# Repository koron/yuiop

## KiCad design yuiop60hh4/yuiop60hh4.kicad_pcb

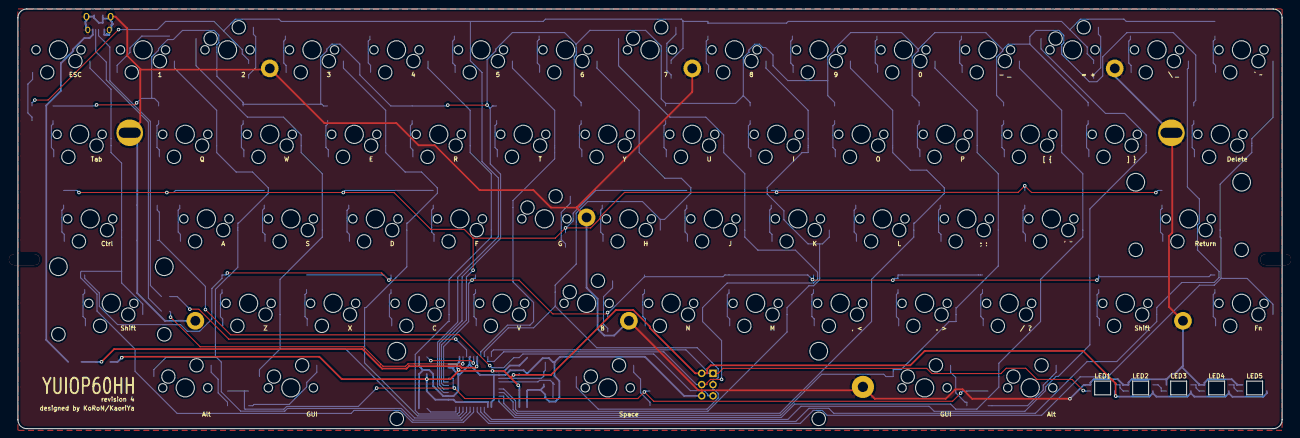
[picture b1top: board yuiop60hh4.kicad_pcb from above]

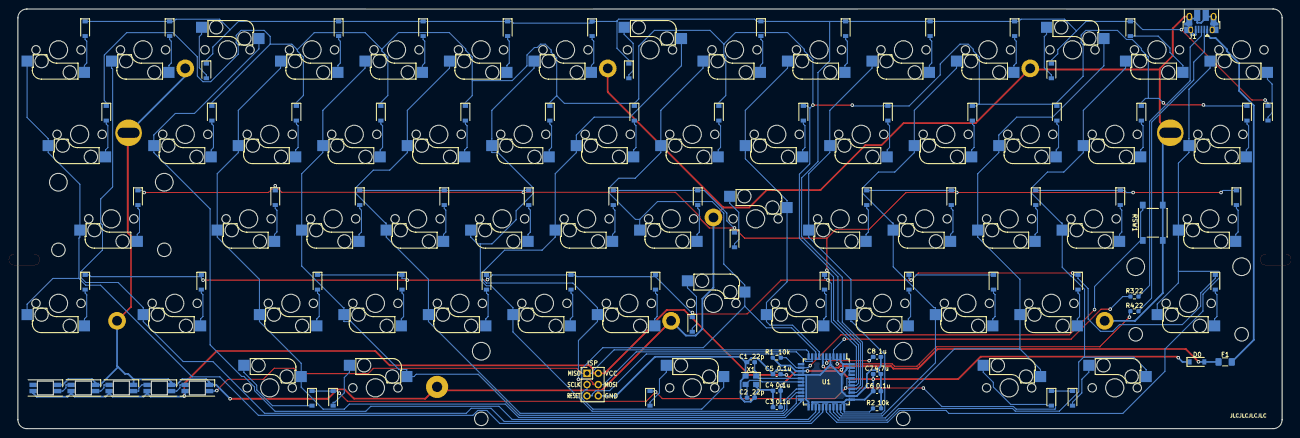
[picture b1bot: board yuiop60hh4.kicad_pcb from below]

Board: 2 copper layers, 285.0 x 94.6 mm, 159 parts (19 on the bottom side), 98 nets.

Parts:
C1, C2: 22p; C_0603_1608Metric_Pad1.08x0.95mm_HandSolder
C3, C4, C5, C6: 0.1u; C_0603_1608Metric_Pad1.08x0.95mm_HandSolder
C7: 4.7u; C_0603_1608Metric_Pad1.08x0.95mm_HandSolder
C8: 1u; C_0603_1608Metric_Pad1.08x0.95mm_HandSolder
D0: D_Schottky; D_SOD-123
D1, D2, D3, D4, D5, D6, D7, D8, D9, D10, D11, D12, D13, D14, D15, D16, D17, D18, D19, D20, D21, D22, D23, D24, D25, D26, D27, D28, D29, D30, D31, D32, D33, D34, D35, D36, D37, D38, D39, D40, D41, D42, D43, D44, D45, D46, D47, D48, D49, D50, D51, D52, D53, D54, D55, D56, D57, D58, D59, D60: 1N4148W; D_SOD-123
F1: Fuse; Fuse_1206_3216Metric_Pad1.42x1.75mm_HandSolder
HOLE1, HOLE2, HOLE4: Hole_5x2.3_6; Hole_5x2.5_7
HOLE3: Hole_2.3; Hole_5x2.5_7
HOLE5, HOLE6: Hole_7x2.5; Hole_7x2.5_10x5
HOLE7, HOLE8, HOLE9, HOLE10, HOLE11, HOLE12: Hole_2.2_4
J1: USB_B_Micro; USB_Micro-B_Amphenol_10103594-0001LF_Horizontal
J2: ISP; PinHeader_2x03_P2.54mm_Vertical
KSW1: ESC; Cherry_MX_Hotswap_1.0u
KSW2: 1; Cherry_MX_Hotswap_1.0u
KSW3: 2; Cherry_MX_Hotswap_1.0u
KSW4: 3; Cherry_MX_Hotswap_1.0u
KSW5: 4; Cherry_MX_Hotswap_1.0u
KSW6: 5; Cherry_MX_Hotswap_1.0u
KSW7: 6; Cherry_MX_Hotswap_1.0u
KSW8: 7; Cherry_MX_Hotswap_1.0u
KSW9: 8; Cherry_MX_Hotswap_1.0u
KSW10: 9; Cherry_MX_Hotswap_1.0u
KSW11: 0; Cherry_MX_Hotswap_1.0u
KSW12: - _; Cherry_MX_Hotswap_1.0u
KSW13: = +; Cherry_MX_Hotswap_1.0u
KSW14: \ _; Cherry_MX_Hotswap_1.0u
KSW15: ` ~~; Cherry_MX_Hotswap_1.0u
KSW16: Tab; Cherry_MX_Hotswap_1.0u
KSW17: Q; Cherry_MX_Hotswap_1.0u
KSW18: W; Cherry_MX_Hotswap_1.0u
KSW19: E; Cherry_MX_Hotswap_1.0u
KSW20: R; Cherry_MX_Hotswap_1.0u
KSW21: T; Cherry_MX_Hotswap_1.0u
KSW22: Y; Cherry_MX_Hotswap_1.0u
KSW23: U; Cherry_MX_Hotswap_1.0u
KSW24: I; Cherry_MX_Hotswap_1.0u
KSW25: O; Cherry_MX_Hotswap_1.0u
KSW26: P; Cherry_MX_Hotswap_1.0u
KSW27: [ {; Cherry_MX_Hotswap_1.0u
KSW28: ] }; Cherry_MX_Hotswap_1.0u
KSW29: Delete; Cherry_MX_Hotswap_1.0u
KSW30: Ctrl; Cherry_MX_Hotswap_1.0u
KSW31: A; Cherry_MX_Hotswap_1.0u
KSW32: S; Cherry_MX_Hotswap_1.0u
KSW33: D; Cherry_MX_Hotswap_1.0u
KSW34: F; Cherry_MX_Hotswap_1.0u
KSW35: G; Cherry_MX_Hotswap_1.0u
KSW36: H; Cherry_MX_Hotswap_1.0u
KSW37: J; Cherry_MX_Hotswap_1.0u
KSW38: K; Cherry_MX_Hotswap_1.0u
KSW39: L; Cherry_MX_Hotswap_1.0u
KSW40: ; :; Cherry_MX_Hotswap_1.0u
KSW41: ' "; Cherry_MX_Hotswap_1.0u
KSW42: Return; Cherry_MX_Hotswap_1.0u
KSW43, KSW54: Shift; Cherry_MX_Hotswap_1.0u
KSW44: Z; Cherry_MX_Hotswap_1.0u
KSW45: X; Cherry_MX_Hotswap_1.0u
KSW46: C; Cherry_MX_Hotswap_1.0u
KSW47: V; Cherry_MX_Hotswap_1.0u
KSW48: B; Cherry_MX_Hotswap_1.0u
KSW49: N; Cherry_MX_Hotswap_1.0u
KSW50: M; Cherry_MX_Hotswap_1.0u
KSW51: , <; Cherry_MX_Hotswap_1.0u
KSW52: . >; Cherry_MX_Hotswap_1.0u
KSW53: / ?; Cherry_MX_Hotswap_1.0u
KSW55: Fn; Cherry_MX_Hotswap_1.0u
KSW56, KSW60: Alt; Cherry_MX_Hotswap_1.0u
KSW57, KSW59: GUI; Cherry_MX_Hotswap_1.0u
KSW58: Space; Cherry_MX_Hotswap_1.0u
LED1, LED2, LED3, LED4, LED5: SK6812MINI; SK6812MINI-E_B
R1, R2: 10k; R_0603_1608Metric_Pad0.98x0.95mm_HandSolder
R3, R4: 22; R_0603_1608Metric_Pad0.98x0.95mm_HandSolder
RSW1: RESET; SW_Push_1P1T_NO_6x6mm_H9.5mm
STB1, STB3: Cherry_MX_Stabilizer
STB2: Cherry_MX_Stabilizer_6.0u
U1: ATmega32U4-AU; TQFP-44_10x10mm_P0.8mm
X1: XTAL; Oscillator_SMD_SeikoEpson_SG8002CE-4Pin_3.2x2.5mm

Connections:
/COL_01: KSW1.1, KSW16.1, KSW30.1, KSW43.1, U1.28
/COL_02: KSW2.1, KSW17.1, KSW31.1, KSW56.1, U1.29
/COL_03: KSW3.1, KSW18.1, KSW32.1, KSW44.1, KSW57.1, U1.30
/COL_04: KSW4.1, KSW19.1, KSW33.1, KSW45.1, U1.31
/COL_05: KSW5.1, KSW20.1, KSW34.1, KSW46.1, U1.32
/COL_06: KSW6.1, KSW21.1, KSW35.1, KSW47.1, U1.8
/COL_07: J2.3, KSW7.1, KSW22.1, KSW36.1, KSW48.1, KSW58.1, U1.9
/COL_08: J2.4, KSW8.1, KSW23.1, KSW37.1, KSW49.1, U1.10
/COL_09: KSW9.1, KSW24.1, KSW38.1, KSW50.1, U1.19
/COL_10: KSW10.1, KSW25.1, KSW39.1, KSW51.1, U1.20
/COL_11: KSW11.1, KSW26.1, KSW40.1, KSW52.1, KSW59.1, U1.21
/COL_12: KSW12.1, KSW27.1, KSW41.1, KSW53.1, KSW60.1, U1.22
/COL_13: KSW13.1, KSW28.1, U1.25
/COL_14: KSW14.1, KSW54.1, U1.26
/COL_15: KSW15.1, KSW29.1, KSW42.1, KSW55.1, U1.27
/Controller/D+: R3.1, U1.4
/Controller/D-: R4.1, U1.3
/Controller/V_USB: D0.2, F1.1, U1.7
/Controller/XTAL1: C2.1, U1.17, X1.3
/Controller/XTAL2: C1.1, U1.16, X1.1
/LED_DATA: J2.1, LED1.4, U1.11
/RESET: J2.5, R1.2, RSW1.1, U1.13
/ROW_1: D1.1, D2.1, D3.1, D4.1, D5.1, D6.1, D7.1, D8.1, D9.1, D10.1, D11.1, D12.1, D13.1, D14.1, D15.1, U1.36
/ROW_2: D16.1, D17.1, D18.1, D19.1, D20.1, D21.1, D22.1, D23.1, D24.1, D25.1, D26.1, D27.1, D28.1, D29.1, U1.37
/ROW_3: D30.1, D31.1, D32.1, D33.1, D34.1, D35.1, D36.1, D37.1, D38.1, D39.1, D40.1, D41.1, D42.1, U1.38
/ROW_4: D43.1, D44.1, D45.1, D46.1, D47.1, D48.1, D49.1, D50.1, D51.1, D52.1, D53.1, D54.1, D55.1, U1.39
/ROW_5: D56.1, D57.1, D58.1, D59.1, D60.1, U1.40
/USB_D+: J1.3, R3.2
/USB_D-: J1.2, R4.2
/USB_VBUS: F1.2, J1.1
GND: C1.2, C2.2, C3.2, C4.2, C5.2, C6.2, C7.2, C8.1, J1.5, J1.6, J2.6, LED1.3, LED2.3, LED3.3, LED4.3, LED5.3, R2.1, RSW1.2, U1.5, U1.15, U1.23, U1.35, U1.43, X1.2, X1.4
unnamed: C8.2, U1.6
unnamed: D1.2, KSW1.2
unnamed: D2.2, KSW2.2
unnamed: D3.2, KSW3.2
unnamed: D4.2, KSW4.2
unnamed: D5.2, KSW5.2
unnamed: D6.2, KSW6.2
unnamed: D7.2, KSW7.2
unnamed: D8.2, KSW8.2
unnamed: D9.2, KSW9.2
unnamed: D10.2, KSW10.2
unnamed: D11.2, KSW11.2
unnamed: D12.2, KSW12.2
unnamed: D13.2, KSW13.2
unnamed: D14.2, KSW14.2
unnamed: D15.2, KSW15.2
unnamed: D16.2, KSW16.2
unnamed: D17.2, KSW17.2
unnamed: D18.2, KSW18.2
unnamed: D19.2, KSW19.2
unnamed: D20.2, KSW20.2
unnamed: D21.2, KSW21.2
unnamed: D22.2, KSW22.2
unnamed: D23.2, KSW23.2
unnamed: D24.2, KSW24.2
unnamed: D25.2, KSW25.2
unnamed: D26.2, KSW26.2
unnamed: D27.2, KSW27.2
unnamed: D28.2, KSW28.2
unnamed: D29.2, KSW29.2
unnamed: D30.2, KSW30.2
unnamed: D31.2, KSW31.2
unnamed: D32.2, KSW32.2
unnamed: D33.2, KSW33.2
unnamed: D34.2, KSW34.2
unnamed: D35.2, KSW35.2
unnamed: D36.2, KSW36.2
unnamed: D37.2, KSW37.2
unnamed: D38.2, KSW38.2
unnamed: D39.2, KSW39.2
unnamed: D40.2, KSW40.2
unnamed: D41.2, KSW41.2
unnamed: D42.2, KSW42.2
unnamed: D43.2, KSW43.2
unnamed: D44.2, KSW44.2
unnamed: D45.2, KSW45.2
unnamed: D46.2, KSW46.2
unnamed: D47.2, KSW47.2
unnamed: D48.2, KSW48.2
unnamed: D49.2, KSW49.2
unnamed: D50.2, KSW50.2
unnamed: D51.2, KSW51.2
unnamed: D52.2, KSW52.2
unnamed: D53.2, KSW53.2
unnamed: D54.2, KSW54.2
unnamed: D55.2, KSW55.2
unnamed: D56.2, KSW56.2
unnamed: D57.2, KSW57.2
unnamed: D58.2, KSW58.2
unnamed: D59.2, KSW59.2
unnamed: D60.2, KSW60.2
unnamed: LED1.2, LED2.4
unnamed: LED2.2, LED3.4
unnamed: LED3.2, LED4.4
unnamed: LED4.2, LED5.4
unnamed: R2.2, U1.33
VCC: C3.1, C4.1, C5.1, C6.1, C7.1, D0.1, J2.2, LED1.1, LED2.1, LED3.1, LED4.1, LED5.1, R1.1, U1.2, U1.14, U1.24, U1.34, U1.44

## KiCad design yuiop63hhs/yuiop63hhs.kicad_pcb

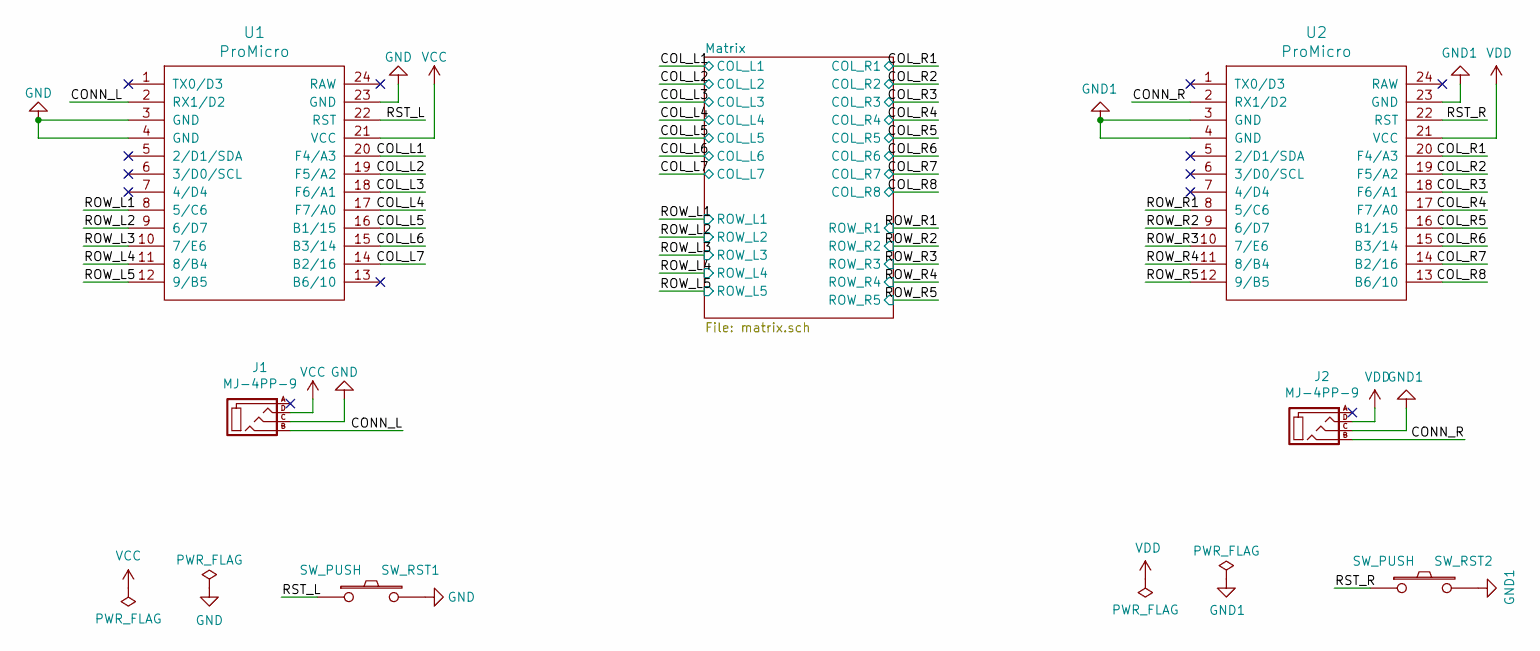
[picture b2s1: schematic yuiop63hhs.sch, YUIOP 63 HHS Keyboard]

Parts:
J1, J2: MJ-4PP-9; MJ-4PP-9_1side
SW_RST1, SW_RST2: SW_PUSH; ResetSW_2_1side
U1, U2: ProMicro; ProMicro_v3

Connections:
/COL_L1: U1.20 (F4/A3); also elsewhere on the board
/COL_L2: U1.19 (F5/A2); also elsewhere on the board
/COL_L3: U1.18 (F6/A1); also elsewhere on the board
/COL_L4: U1.17 (F7/A0); also elsewhere on the board
/COL_L5: U1.16 (B1/15); also elsewhere on the board
/COL_L6: U1.15 (B3/14); also elsewhere on the board
/COL_L7: U1.14 (B2/16); also elsewhere on the board
/COL_R1: U2.20 (F4/A3); also elsewhere on the board
/COL_R2: U2.19 (F5/A2); also elsewhere on the board
/COL_R3: U2.18 (F6/A1); also elsewhere on the board
/COL_R4: U2.17 (F7/A0); also elsewhere on the board
/COL_R5: U2.16 (B1/15); also elsewhere on the board
/COL_R6: U2.15 (B3/14); also elsewhere on the board
/COL_R7: U2.14 (B2/16); also elsewhere on the board
/COL_R8: U2.13 (B6/10); also elsewhere on the board
/CONN_L: J1.B, U1.2 (RX1/D2)
/CONN_R: J2.B, U2.2 (RX1/D2)
/ROW_L1: U1.8 (5/C6); also elsewhere on the board
/ROW_L2: U1.9 (6/D7); also elsewhere on the board
/ROW_L3: U1.10 (7/E6); also elsewhere on the board
/ROW_L4: U1.11 (8/B4); also elsewhere on the board
/ROW_L5: U1.12 (9/B5); also elsewhere on the board
/ROW_R1: U2.8 (5/C6); also elsewhere on the board
/ROW_R2: U2.9 (6/D7); also elsewhere on the board
/ROW_R3: U2.10 (7/E6); also elsewhere on the board
/ROW_R4: U2.11 (8/B4); also elsewhere on the board
/ROW_R5: U2.12 (9/B5); also elsewhere on the board
/RST_L: SW_RST1.1, U1.22 (RST)
/RST_R: SW_RST2.1, U2.22 (RST)
GND: J1.C, SW_RST1.2, U1.3 (GND), U1.4 (GND), U1.23 (GND)
GND1: J2.C, SW_RST2.2, U2.3 (GND), U2.4 (GND), U2.23 (GND)
VCC: J1.D, U1.21 (VCC)
VDD: J2.D, U2.21 (VCC)

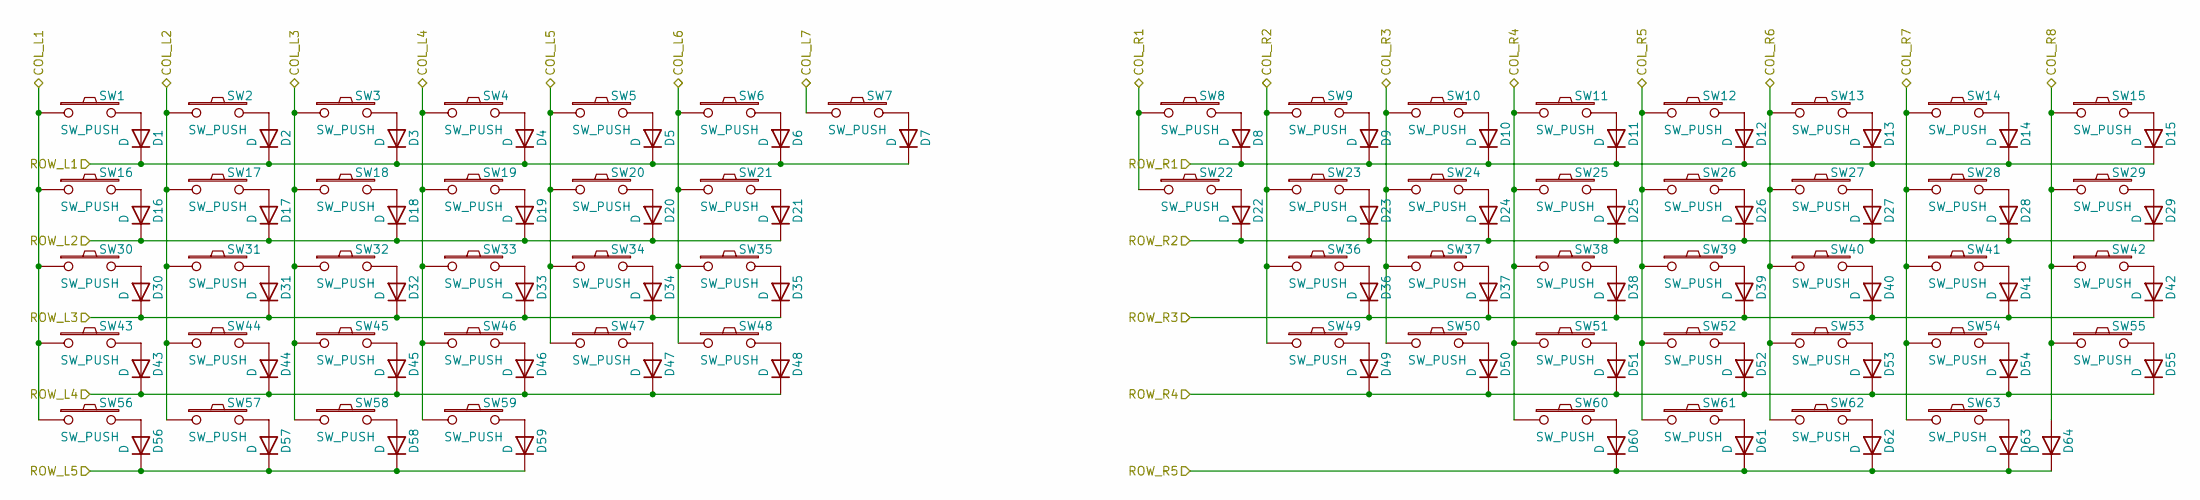
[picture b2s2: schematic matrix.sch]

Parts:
D1, D2, D3, D4, D5, D6, D7, D8, D9, D10, D11, D12, D13, D14, D15, D16, D17, D18, D19, D20, D21, D22, D23, D24, D25, D26, D27, D28, D29, D30, D31, D32, D33, D34, D35, D36, D37, D38, D39, D40, D41, D42, D43, D44, D45, D46, D47, D48, D49, D50, D51, D52, D53, D54, D55, D56, D57, D58, D59, D60, D61, D62, D63, D64: D; D3_SMD_v2_B
SW1, SW2, SW3, SW4, SW5, SW6, SW7, SW8, SW9, SW10, SW11, SW12, SW13, SW14, SW15, SW16, SW17, SW18, SW19, SW20, SW21, SW22, SW23, SW24, SW25, SW26, SW27, SW28, SW29, SW30, SW31, SW32, SW33, SW34, SW35, SW36, SW37, SW38, SW39, SW40, SW41, SW42, SW43, SW44, SW45, SW46, SW47, SW48, SW49, SW50, SW51, SW52, SW53, SW54, SW55, SW56, SW57, SW58, SW59, SW60, SW61, SW62, SW63: SW_PUSH; Switch_CherryMX_1.00u

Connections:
/COL_L1: SW1.1, SW16.1, SW30.1, SW43.1, SW56.1; also elsewhere on the board
/COL_L2: SW2.1, SW17.1, SW31.1, SW44.1, SW57.1; also elsewhere on the board
/COL_L3: SW3.1, SW18.1, SW32.1, SW45.1, SW58.1; also elsewhere on the board
/COL_L4: SW4.1, SW19.1, SW33.1, SW46.1, SW59.1; also elsewhere on the board
/COL_L5: SW5.1, SW20.1, SW34.1, SW47.1; also elsewhere on the board
/COL_L6: SW6.1, SW21.1, SW35.1, SW48.1; also elsewhere on the board
/COL_L7: SW7.1; also elsewhere on the board
/COL_R1: SW8.1, SW22.1; also elsewhere on the board
/COL_R2: SW9.1, SW23.1, SW36.1, SW49.1; also elsewhere on the board
/COL_R3: SW10.1, SW24.1, SW37.1, SW50.1; also elsewhere on the board
/COL_R4: SW11.1, SW25.1, SW38.1, SW51.1, SW60.1; also elsewhere on the board
/COL_R5: SW12.1, SW26.1, SW39.1, SW52.1, SW61.1; also elsewhere on the board
/COL_R6: SW13.1, SW27.1, SW40.1, SW53.1, SW62.1; also elsewhere on the board
/COL_R7: SW14.1, SW28.1, SW41.1, SW54.1, SW63.1; also elsewhere on the board
/COL_R8: D64.2 (A), SW15.1, SW29.1, SW42.1, SW55.1; also elsewhere on the board
/ROW_L1: D1.1 (K), D2.1 (K), D3.1 (K), D4.1 (K), D5.1 (K), D6.1 (K), D7.1 (K); also elsewhere on the board
/ROW_L2: D16.1 (K), D17.1 (K), D18.1 (K), D19.1 (K), D20.1 (K), D21.1 (K); also elsewhere on the board
/ROW_L3: D30.1 (K), D31.1 (K), D32.1 (K), D33.1 (K), D34.1 (K), D35.1 (K); also elsewhere on the board
/ROW_L4: D43.1 (K), D44.1 (K), D45.1 (K), D46.1 (K), D47.1 (K), D48.1 (K); also elsewhere on the board
/ROW_L5: D56.1 (K), D57.1 (K), D58.1 (K), D59.1 (K); also elsewhere on the board
/ROW_R1: D8.1 (K), D9.1 (K), D10.1 (K), D11.1 (K), D12.1 (K), D13.1 (K), D14.1 (K), D15.1 (K); also elsewhere on the board
/ROW_R2: D22.1 (K), D23.1 (K), D24.1 (K), D25.1 (K), D26.1 (K), D27.1 (K), D28.1 (K), D29.1 (K); also elsewhere on the board
/ROW_R3: D36.1 (K), D37.1 (K), D38.1 (K), D39.1 (K), D40.1 (K), D41.1 (K), D42.1 (K); also elsewhere on the board
/ROW_R4: D49.1 (K), D50.1 (K), D51.1 (K), D52.1 (K), D53.1 (K), D54.1 (K), D55.1 (K); also elsewhere on the board
/ROW_R5: D60.1 (K), D61.1 (K), D62.1 (K), D63.1 (K), D64.1 (K); also elsewhere on the board
unnamed: D1.2 (A), SW1.2
unnamed: D2.2 (A), SW2.2
unnamed: D3.2 (A), SW3.2
unnamed: D4.2 (A), SW4.2
unnamed: D5.2 (A), SW5.2
unnamed: D6.2 (A), SW6.2
unnamed: D7.2 (A), SW7.2
unnamed: D8.2 (A), SW8.2
unnamed: D9.2 (A), SW9.2
unnamed: D10.2 (A), SW10.2
unnamed: D11.2 (A), SW11.2
unnamed: D12.2 (A), SW12.2
unnamed: D13.2 (A), SW13.2
unnamed: D14.2 (A), SW14.2
unnamed: D15.2 (A), SW15.2
unnamed: D16.2 (A), SW16.2
unnamed: D17.2 (A), SW17.2
unnamed: D18.2 (A), SW18.2
unnamed: D19.2 (A), SW19.2
unnamed: D20.2 (A), SW20.2
unnamed: D21.2 (A), SW21.2
unnamed: D22.2 (A), SW22.2
unnamed: D23.2 (A), SW23.2
unnamed: D24.2 (A), SW24.2
unnamed: D25.2 (A), SW25.2
unnamed: D26.2 (A), SW26.2
unnamed: D27.2 (A), SW27.2
unnamed: D28.2 (A), SW28.2
unnamed: D29.2 (A), SW29.2
unnamed: D30.2 (A), SW30.2
unnamed: D31.2 (A), SW31.2
unnamed: D32.2 (A), SW32.2
unnamed: D33.2 (A), SW33.2
unnamed: D34.2 (A), SW34.2
unnamed: D35.2 (A), SW35.2
unnamed: D36.2 (A), SW36.2
unnamed: D37.2 (A), SW37.2
unnamed: D38.2 (A), SW38.2
unnamed: D39.2 (A), SW39.2
unnamed: D40.2 (A), SW40.2
unnamed: D41.2 (A), SW41.2
unnamed: D42.2 (A), SW42.2
unnamed: D43.2 (A), SW43.2
unnamed: D44.2 (A), SW44.2
unnamed: D45.2 (A), SW45.2
unnamed: D46.2 (A), SW46.2
unnamed: D47.2 (A), SW47.2
unnamed: D48.2 (A), SW48.2
unnamed: D49.2 (A), SW49.2
unnamed: D50.2 (A), SW50.2
unnamed: D51.2 (A), SW51.2
unnamed: D52.2 (A), SW52.2
unnamed: D53.2 (A), SW53.2
unnamed: D54.2 (A), SW54.2
unnamed: D55.2 (A), SW55.2
unnamed: D56.2 (A), SW56.2
unnamed: D57.2 (A), SW57.2
unnamed: D58.2 (A), SW58.2
unnamed: D59.2 (A), SW59.2
unnamed: D60.2 (A), SW60.2
unnamed: D61.2 (A), SW61.2
unnamed: D62.2 (A), SW62.2
unnamed: D63.2 (A), SW63.2

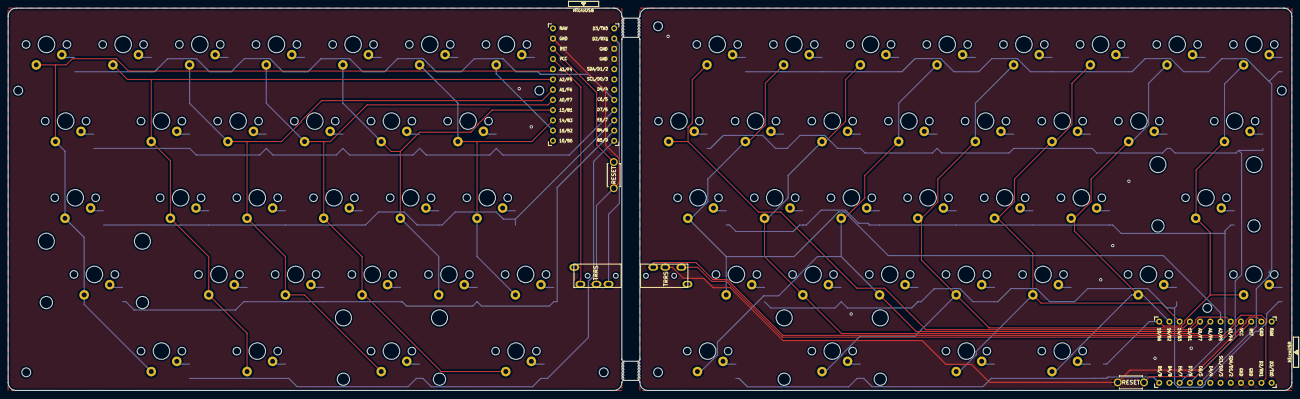
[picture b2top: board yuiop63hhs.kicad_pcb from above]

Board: 2 copper layers, 319.0 x 95.0 mm, 137 parts (0 on the bottom side), 96 nets.

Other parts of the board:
STB1, STB2, STB3, STB4: Cherry_MX_Stabilizer

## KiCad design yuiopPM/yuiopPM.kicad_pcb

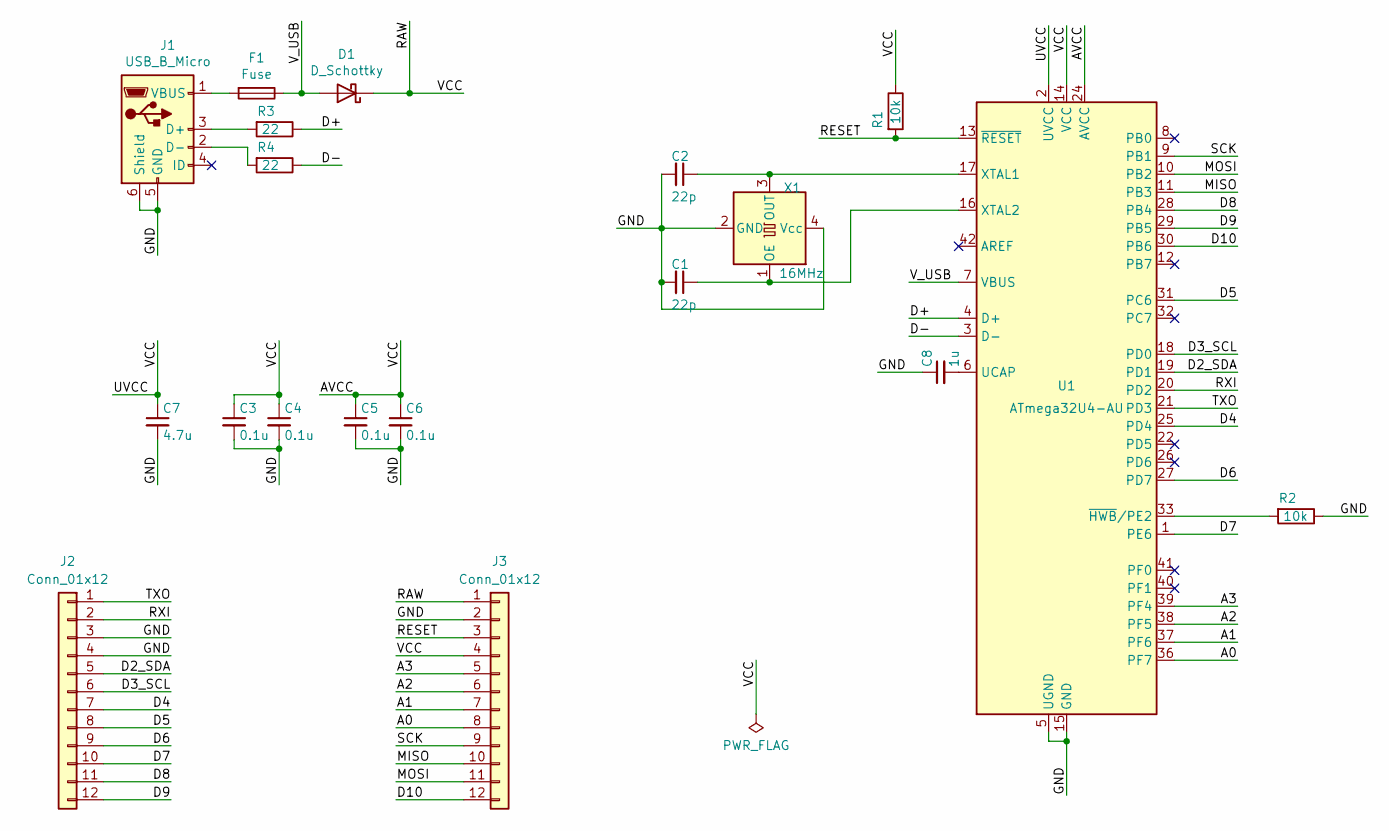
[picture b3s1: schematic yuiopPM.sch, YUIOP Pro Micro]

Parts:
C1, C2: 22p; C_0603_1608Metric
C3, C4, C5, C6: 0.1u; C_0603_1608Metric
C7: 4.7u; C_0603_1608Metric
C8: 1u; C_0603_1608Metric
D1: D_Schottky; D_SOD-123
F1: Fuse; Fuse_1206_3216Metric
J1: USB_B_Micro; USB-MicroB_ZX62M-B-5P
J2, J3: Conn_01x12; SpringPinHeader-01x12
R1, R2: 10k; R_0603_1608Metric
R3, R4: 22; R_0603_1608Metric
U1: ATmega32U4-AU; TQFP-44_10x10mm_P0.8mm
X1: 16MHz; Oscillator_SMD_SeikoEpson_SG8002CE-4Pin_3.2x2.5mm

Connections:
/A0: J3.8, U1.36 (PF7)
/A1: J3.7, U1.37 (PF6)
/A2: J3.6, U1.38 (PF5)
/A3: J3.5, U1.39 (PF4)
/AVCC: C3.1, C4.1, C5.1, C6.1, C7.1, D1.1 (K), J3.1, J3.4, R1.1, U1.2 (UVCC), U1.14 (VCC), U1.24 (AVCC), U1.34 (VCC), U1.44 (AVCC)
/D2_SDA: J2.5, U1.19 (PD1)
/D3_SCL: J2.6, U1.18 (PD0)
/D4: J2.7, U1.25 (PD4)
/D5: J2.8, U1.31 (PC6)
/D6: J2.9, U1.27 (PD7)
/D7: J2.10, U1.1 (PE6)
/D8: J2.11, U1.28 (PB4)
/D9: J2.12, U1.29 (PB5)
/D10: J3.12, U1.30 (PB6)
/D+: R3.1, U1.4 (D+)
/D-: R4.1, U1.3 (D-)
/GND: C1.2, C2.2, C3.2, C4.2, C5.2, C6.2, C7.2, C8.1, J1.5 (GND), J1.6 (Shield), J2.3, J2.4, J3.2, R2.1, U1.5 (UGND), U1.15 (GND), U1.23 (GND), U1.35 (GND), U1.43 (GND), X1.2 (GND), X1.4 (Vcc)
/MISO: J3.10, U1.11 (PB3)
/MOSI: J3.11, U1.10 (PB2)
/RESET: J3.3, R1.2, U1.13 (~RESET)
/RXI: J2.2, U1.20 (PD2)
/SCK: J3.9, U1.9 (PB1)
/TXO: J2.1, U1.21 (PD3)
/V_USB: D1.2 (A), F1.1, U1.7 (VBUS)
unnamed: C1.1, U1.16 (XTAL2), X1.1 (OE)
unnamed: C2.1, U1.17 (XTAL1), X1.3 (OUT)
unnamed: C8.2, U1.6 (UCAP)
unnamed: F1.2, J1.1 (VBUS)
unnamed: J1.2 (D-), R4.2
unnamed: J1.3 (D+), R3.2
unnamed: R2.2, U1.33 (~HWB~/PE2)

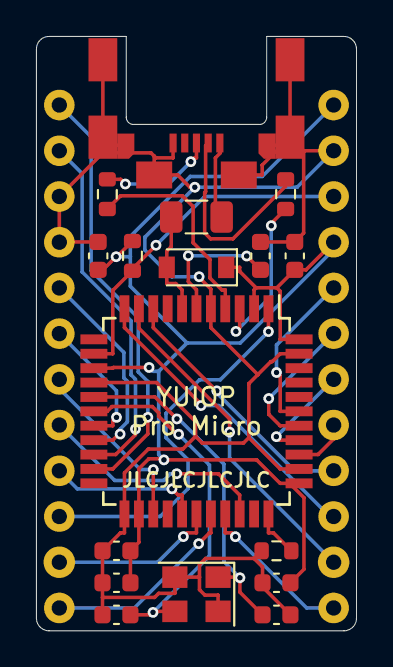
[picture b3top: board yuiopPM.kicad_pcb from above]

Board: 2 copper layers, 17.8 x 33.0 mm, 19 parts (0 on the bottom side), 31 nets.
